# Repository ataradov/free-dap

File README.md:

# Free-DAP

This is a free and open implementation of the CMSIS-DAP debugger firmware.

Both SWD and JTAG protocols are supported. However JTAG was not well tested due to lack of
good targets. If you have any issues with it - let me know and I'll try to help.

## Software Changes

This forked branch is for _**Jeff Probe**_ with the following changes:
 * Three status LEDs: Yellow for VCP connection, Orange for DAP, the Red for power indicator
 * The brightness for three status LEDs has been reduced to 5% via PWM as they are too bright to view directly.
 * Implemented ADC power supply sensing, the threshold is 1.1V. If the power is supplied by _**Jeff Probe**_, Power indicator is solid on. If the power is supplied by target device itself, the power indicator is blinking 
 * Implemented Button click and hold detection. Currently the following actions are defined:
    - Single Click: Turn on/off the power to the target board using _**Jeff Probe**_'s internal 3.3v LDO
    - Double Click + Hold: Reboot the device ( when combining with [this bootloader](https://github.com/hlyi/uf2-samdx1), it can easily reflash new version of the FW)
 * Implemented ramping up power to target board. This feature require a hardware modification.
 * Added TMS_DIR control that used by _**Jeff Probe**_
 * Added configuration to support active high reset control as used by _**Jeff Probe**_

## Hardware Modification

The POWER_TGT signal (the control signal to provide 3.3V power to the tagret board) in the original _**Jeff Probe**_ is on PA28. Simply toggling this GPIO pin causes brownout problem on my setup due to in-rush current to the target board. Unfortunately, this pin doesn't support PWM function. The hardware mod is to connect PA01 (pin 2) to PA28 (pin 27) via 300 Ohm resistor ( the resistor is not absolutely required, but was added to protect against bad firmware)

## TODO List
 * Add _reset sensing_. This feature is supported by _**Jeff Probe**_ hardware
 * Use button _double click_ to cycling between the following modes:
   - DAP v1 (HID) + DAP v2 + VCP
   - DAP v1 (HID) + VCP + Custom HID
   - DAP v2 (HID) + VCP + Custom HID
 * The custon HID can
   - Provide target board voltage readout
   - Provide debugging information from _Free DAP_ firmware itself
   - Control power supply to the target board ( similar to button single click )
   - and more...

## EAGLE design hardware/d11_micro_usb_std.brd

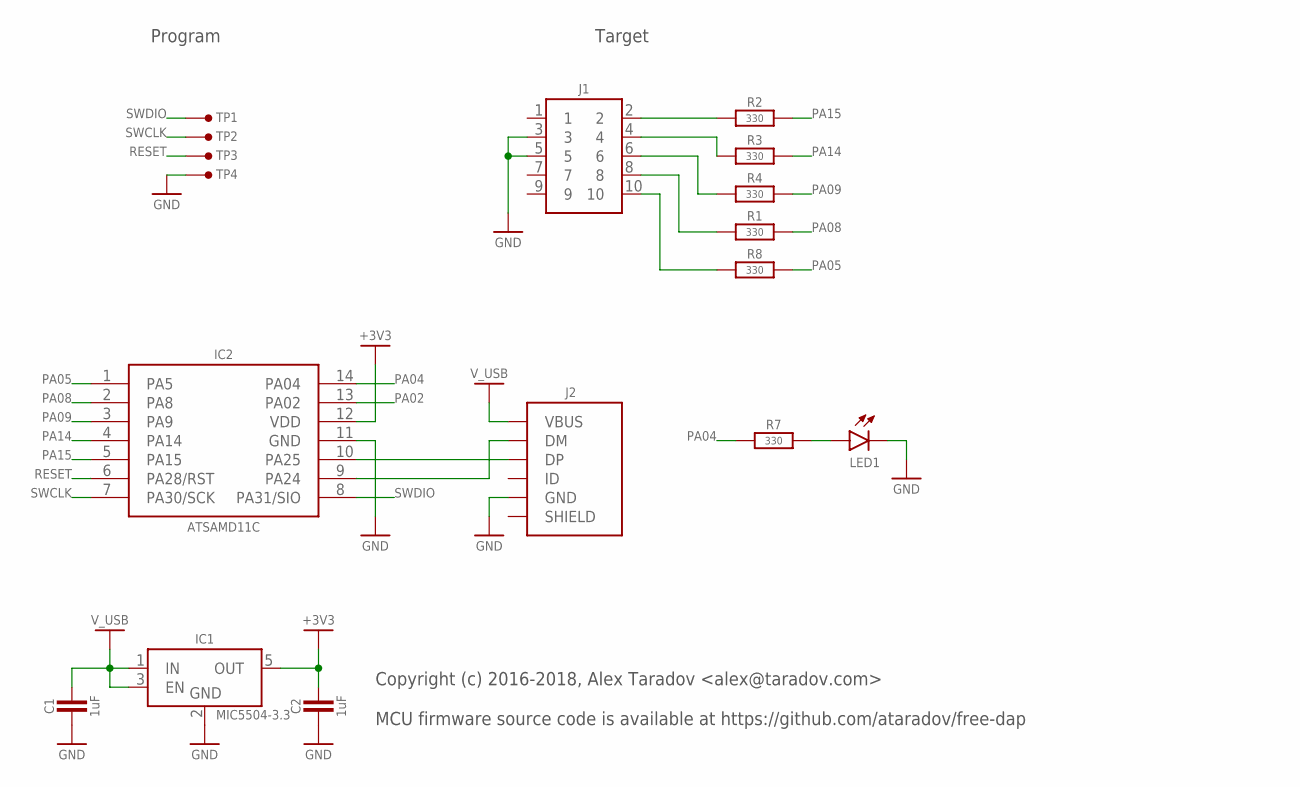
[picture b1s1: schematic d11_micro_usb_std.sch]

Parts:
C1, C2: 1uF; SMD0603
IC1: MIC5504-3.3; SOT23-5
IC2: ATSAMD11C; SO-14
J1: HEADER-5X2-TH-1.27; HEADER-5X2-1.27MM
J2: USB-B-MICRO-SMT; USB-B-MICRO-SMT-SHELL-TH
LED1: LED_SMDLED_0603; SMD0603
R1, R2, R3, R4, R7, R8: 330; SMD0603
TP1: SIO; TP-1.27MM
TP2, TP3, TP4: TEST-POINT-1.27MM; TP-1.27MM

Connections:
+3V3: C2.2, IC1.5 (OUT), IC2.12 (VDD)
GND: C1.1, C2.1, IC1.2 (GND), IC2.11 (GND), J1.3, J1.5, J2.5 (GND), LED1.2 (C), TP4.1
unnamed: IC2.9 (PA24), J2.2 (DM)
unnamed: IC2.10 (PA25), J2.3 (DP)
unnamed: LED1.1 (A), R7.2
unnamed: J1.2, R2.1
unnamed: J1.4, R3.1
unnamed: J1.6, R4.1
unnamed: J1.8, R1.1
unnamed: J1.10, R8.1
PA02: IC2.13 (PA02)
PA04: IC2.14 (PA04), R7.1
PA05: IC2.1 (PA5), R8.2
PA08: IC2.2 (PA8), R1.2
PA09: IC2.3 (PA9), R4.2
PA14: IC2.4 (PA14), R3.2
PA15: IC2.5 (PA15), R2.2
RESET: IC2.6 (PA28/RST), TP3.1
SWCLK: IC2.7 (PA30/SCK), TP2.1
SWDIO: IC2.8 (PA31/SIO), TP1.1
V_USB: C1.2, IC1.1 (IN), IC1.3 (EN), J2.1 (VBUS)

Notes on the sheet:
Program
Target
Copyright (c) 2016-2018, Alex Taradov <alex@taradov.com> MCU firmware source code is available at https://github.com/ataradov/free-dap

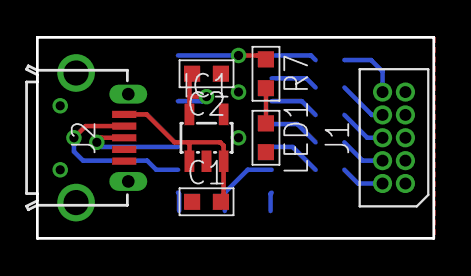
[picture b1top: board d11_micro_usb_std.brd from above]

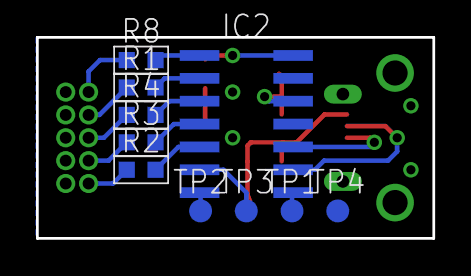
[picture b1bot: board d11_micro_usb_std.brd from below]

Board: 2 copper layers, 22.0 x 11.2 mm, 17 parts (10 on the bottom side), 20 nets.

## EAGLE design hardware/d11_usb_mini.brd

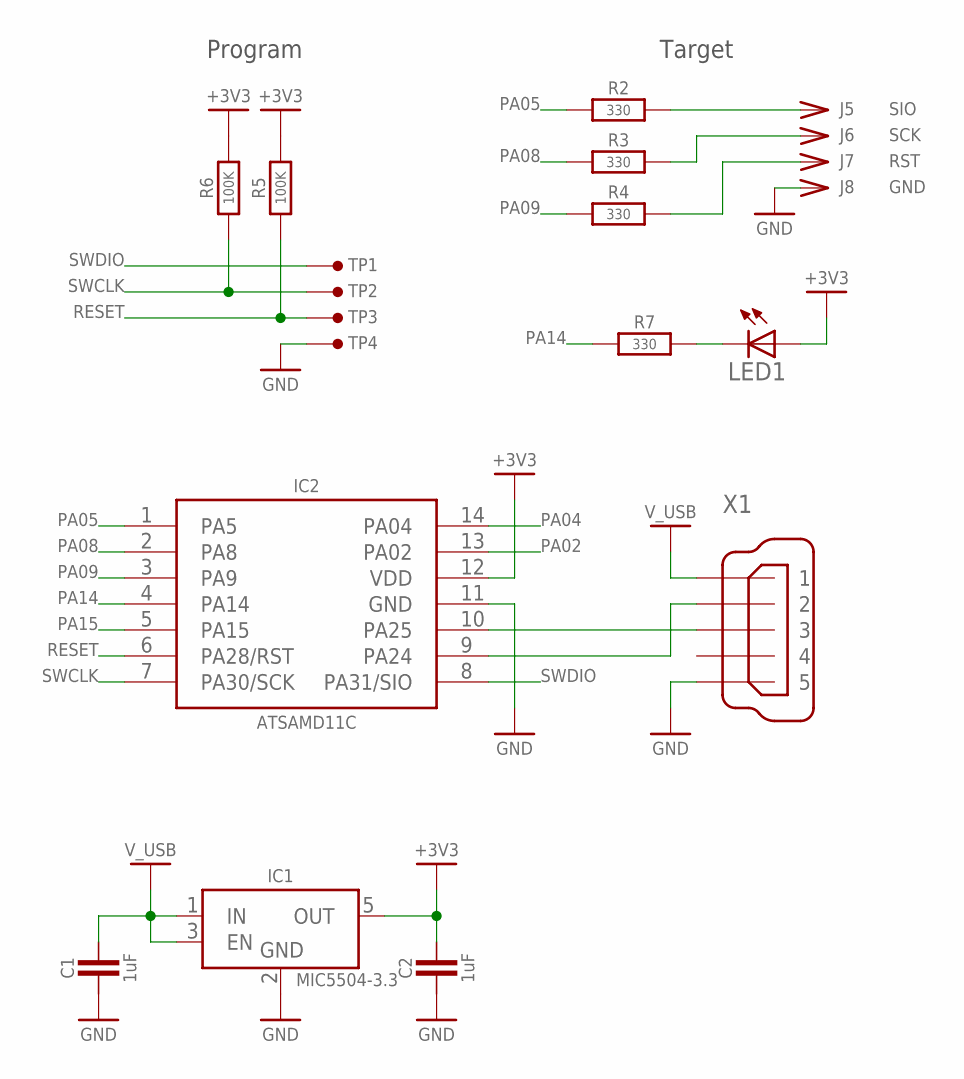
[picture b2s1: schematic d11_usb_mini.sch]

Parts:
C1, C2: 1uF; SMD0603
IC1: MIC5504-3.3; SOT23-5
IC2: ATSAMD11C; SO-14
J5: SIO; PIN-TH
J6: SCK; PIN-TH
J7: RST; PIN-TH
J8: GND; PIN-TH
LED1: LEDCHIPLED_0603; CHIPLED_0603
R2, R3, R4, R7: 330; SMD0603
R5, R6: 100K; SMD0603
TP1: SIO; TP-1.27MM
TP2, TP3, TP4: TEST-POINT-1.27MM; TP-1.27MM
X1: MINI-USB-32005-201; 32005-201

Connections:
+3V3: C2.2, IC1.5 (OUT), IC2.12 (VDD), LED1.A, R5.2, R6.2
GND: C1.1, C2.1, IC1.2 (GND), IC2.11 (GND), J8.1, TP4.1, X1.5
unnamed: IC2.9 (PA24), X1.2
unnamed: IC2.10 (PA25), X1.3
unnamed: J5.1, R2.2
unnamed: J6.1, R3.2
unnamed: J7.1, R4.2
unnamed: LED1.C, R7.2
PA02: IC2.13 (PA02)
PA04: IC2.14 (PA04)
PA05: IC2.1 (PA5), R2.1
PA08: IC2.2 (PA8), R3.1
PA09: IC2.3 (PA9), R4.1
PA14: IC2.4 (PA14), R7.1
PA15: IC2.5 (PA15)
RESET: IC2.6 (PA28/RST), R5.1, TP3.1
SWCLK: IC2.7 (PA30/SCK), R6.1, TP2.1
SWDIO: IC2.8 (PA31/SIO), TP1.1
V_USB: C1.2, IC1.1 (IN), IC1.3 (EN), X1.1

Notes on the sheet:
Program
Target

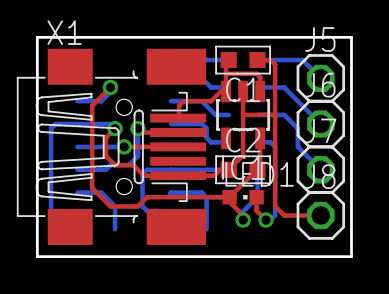
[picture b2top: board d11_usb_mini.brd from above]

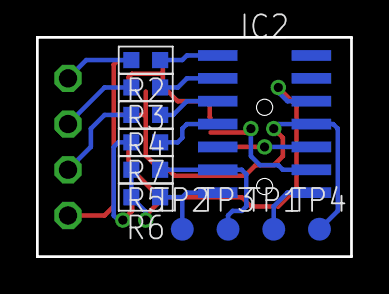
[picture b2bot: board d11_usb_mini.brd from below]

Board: 2 copper layers, 17.4 x 12.2 mm, 20 parts (11 on the bottom side), 16 nets.

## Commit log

2016-07-18 Initial implementation
2016-07-18 Implemented LED logic
2017-01-21 Added SAM D11 support
2017-01-25 Added SAM D11 hardware reference design
2017-01-27 Minor hardware changes + bootloader mode
2017-03-18 Added PDF version of the schematic
2017-03-25 Added a version with a standard connector
2017-05-08 Added support for SWD USB STD board
2017-05-10 Added variable serial number (via UID of the device)
2017-05-10 Added variable serial number (now in DAP as well)
2018-01-28 add const declarations
2018-01-29 Removed warnings after const declarations
2018-05-26 Added Micro-USB version
2018-06-03 Updated resistor values to actually used on the boards
2018-09-09 Increase USB buffer size
    When defining a long product name, it might not be transferred correctly via USB HID since the string is cut.
2018-09-18 Removed string descriptor buffer
2019-04-14 Added combined CMSIS-DAP and VCP version (hardweare not tested yet)
2019-04-14 Added combined CMSIS-DAP and VCP firmware (tested on a dev kit only)
2019-04-26 Modifications for the final hardware
2019-08-28 Convert to LF file endings
2019-08-28 Detect proper mkdir
2019-10-01 Proper selection of mkdir depending on the OS
2019-11-01 Robustness increase
2020-02-23 Line endigs fix and transfer abort fix
2020-02-23 Serial Number termination fix
2020-02-23 Added SAM E70 platform
2020-10-28 New HID descriptors to make MAC OS happy.
2021-03-07 Added response payload size calculation for non-HID transfer layers
2021-03-07 Moved some hardware files around
2021-03-20 Added bootloader support and some minor fixes
2021-04-10 Centralized pin configuration
2021-04-12 Centralized pin configuration
    USB pin configuration is not moved into header, since it cannot reasonably be changed on SAMD11 platform. In order to change the UART pin configuration, the SERCOM interface configuration has to be c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
2021-05-14 Major refactor plus added JTAG support
2021-05-16 Exposed buffer manipulation functions
2021-05-27 Added VCP V3 board support and DFU bootloader support
2021-05-27 Added pogo-pin D11 board
2021-05-27 Modified clock settings
2021-05-27 Minor Makefile fix
2021-05-27 Added 2K DFU bootloader versions
2021-05-30 Minor JTAG speed improvement
2021-10-01 add dap_init() at beginning of main() for same70
2021-11-07 Changed default board version
2021-11-07 Added V2 of the standard debugger board
2021-11-07 Added V4 of the VCP debugger board (no FW support yet)
2021-12-23 Fidex TDI write in dap_swj_pins()
2022-01-05 Added RP2040 support
2022-01-05 Added binary file for RP2040
2022-01-05 Typo fix
2022-03-03 Added new info strings and version information
2022-03-05 Fixed an error in string length calculation
2022-03-05 Added CMSIS-DAP v2 support to RP2040 port + some USB code refactoring
2022-03-05 Binay update
2022-03-06 Updated CMSIS-DAP version to v2
2022-03-06 Implemented CMSIS-DAP v2 for SAM D11, combined VCP and non-VCP versions into one platform
2022-04-03 Build free-dap using GitHub Actions
    Building the different platforms using multiple steps instead of multiple jobs since each build is quite small, thus using multiple jobs would take far longer on CI
2022-04-03 Define HAL_BOARD only if not already defined
    By defining HAL_BOARD_VCP_V3 iff not already another board is defined, the hal configuration can be changed by compiler flags.
2022-04-03 Provide HAL_BOARD_CUSTOM as injection point for custom HAL configuration
2022-04-04 Removed tools directory
2022-04-04 Added bin2uf2 information to the readme
2022-04-04 Created Makefile variable for a bin2uf2 tool
2022-04-04 Added custom board support
2022-04-07 Added a new D11-based board
2022-04-21 Clear error status bits in UART driver
2022-04-22 Added smaller version of the standard board with USB Type-C connector
2022-07-20 Added Nuvoton M484 support
2022-07-20 Removed extra USB drivers
2022-07-31 Implemented 2 DAP buffers (for SAM D11 for now)
2022-08-05 Added M484-based hardware
2022-08-07 Fixed multiple DAP buffers
2022-08-27 Add nuvoton usb fs impl for m482
2022-08-27 Re-enable recv and use -Os again
2022-08-27 Read more if it got a full packet
2023-07-22 try to refactor samd11 code so samd21 can reuse
2023-07-22 add support for devices that TMS has explicit direction control (for level-shifter)
2023-07-22 update jeff probe hal configuration for TMS direction
2023-07-22 clean redefine warning
2023-07-22 Add LED if HAL_CONFIG_HAS_PWR_STATUS is set Add define for supplying power to target Add option separate nRESET control and nRESET sense Add otpion for nRESET to be active high
2023-07-23 add HAL_CONFIG_CUSTOM_LED to enable custom LED turn on/off function. It has been used for Jeff Probe for brightness control of LEDs
2023-09-09 enable power output
2024-01-13 Updated SAM D21 implementation
2024-01-21 Add jeff probe
2024-01-21 move dap enhancement to samd11 to samd21
2024-01-21 sync to master branch
2024-01-22 update binary filename
2024-01-22 fix pin configuration for jeff probe
2024-01-22 add support for ADC sensing power supply
2024-01-22 turn on or blinking power led based upon if target had power
2024-01-24 add button handling: one click to turn on power, double click and hold to reboot to bootloader
2024-01-25 change power control pin from PA28 to PA01 (HW mod) in order to enable PWM mode for powering up external supply
